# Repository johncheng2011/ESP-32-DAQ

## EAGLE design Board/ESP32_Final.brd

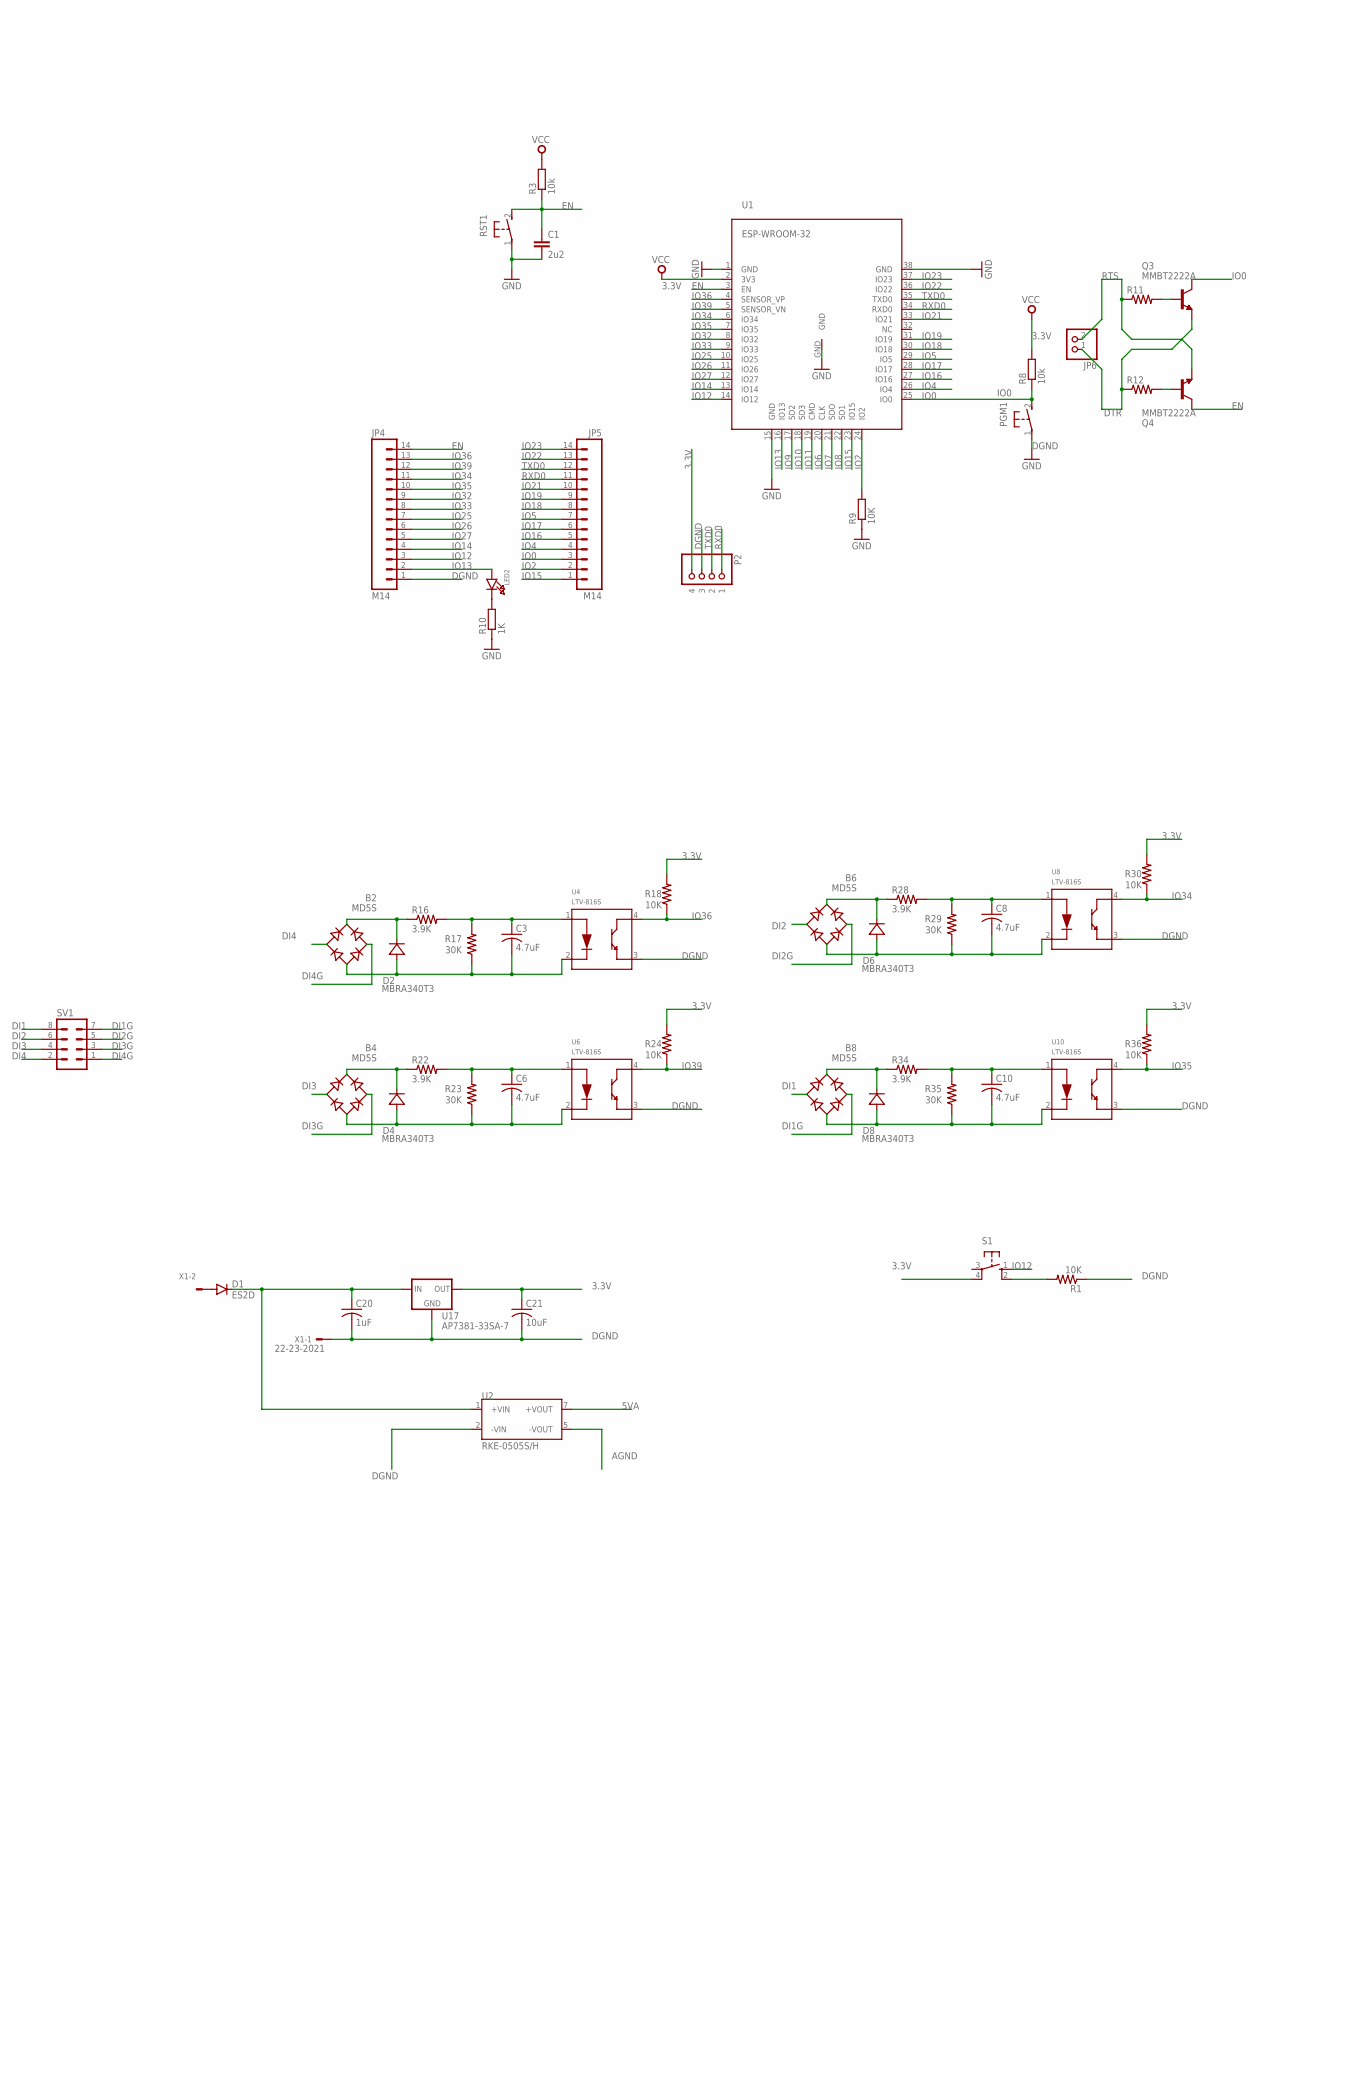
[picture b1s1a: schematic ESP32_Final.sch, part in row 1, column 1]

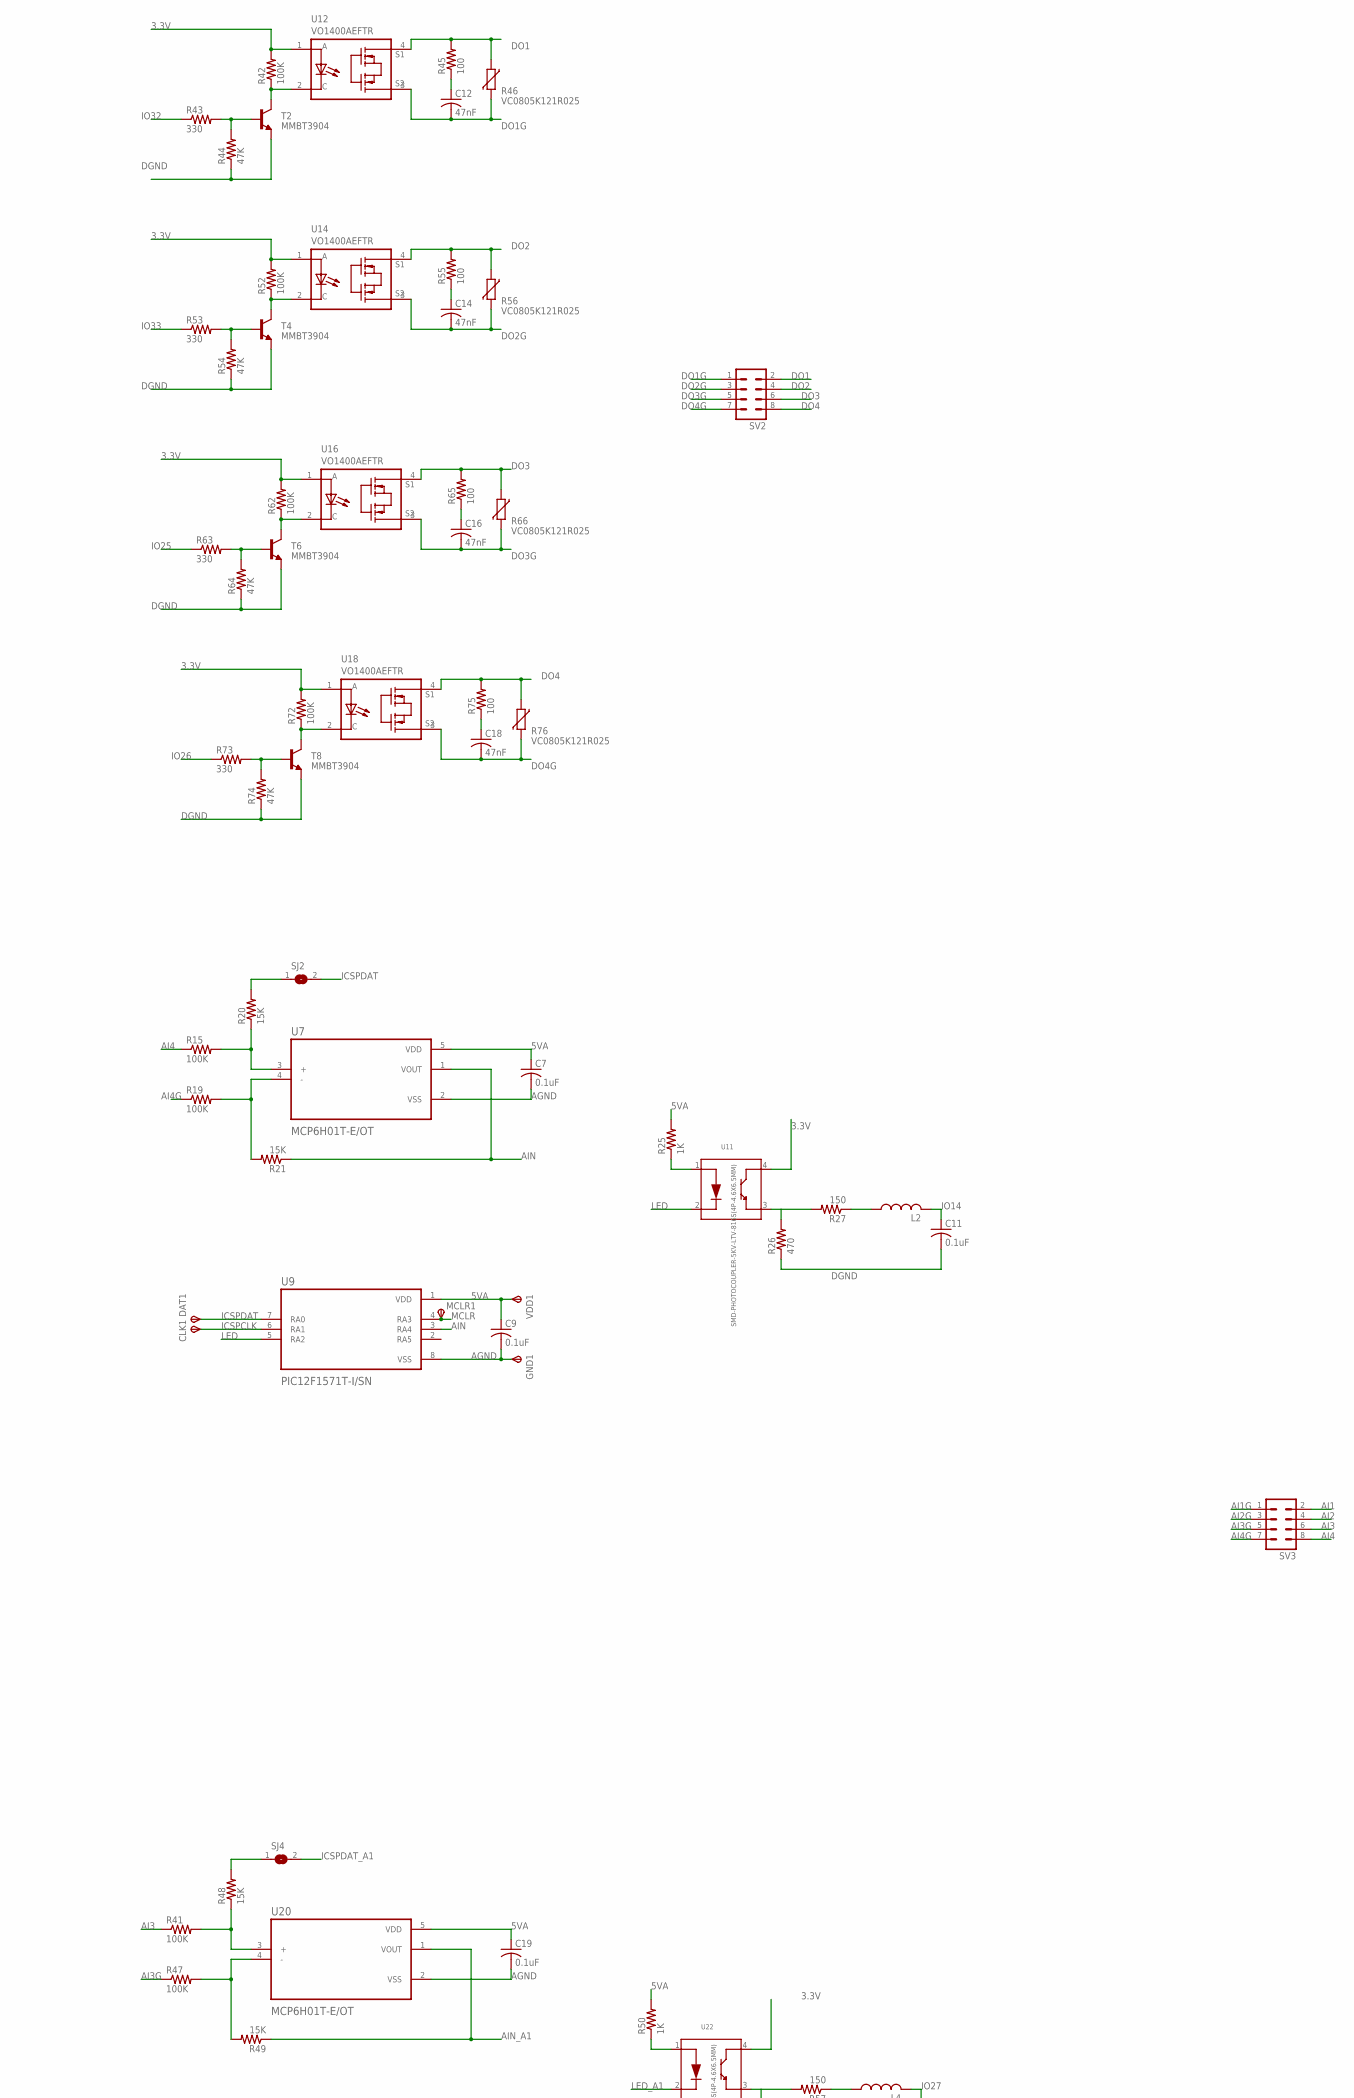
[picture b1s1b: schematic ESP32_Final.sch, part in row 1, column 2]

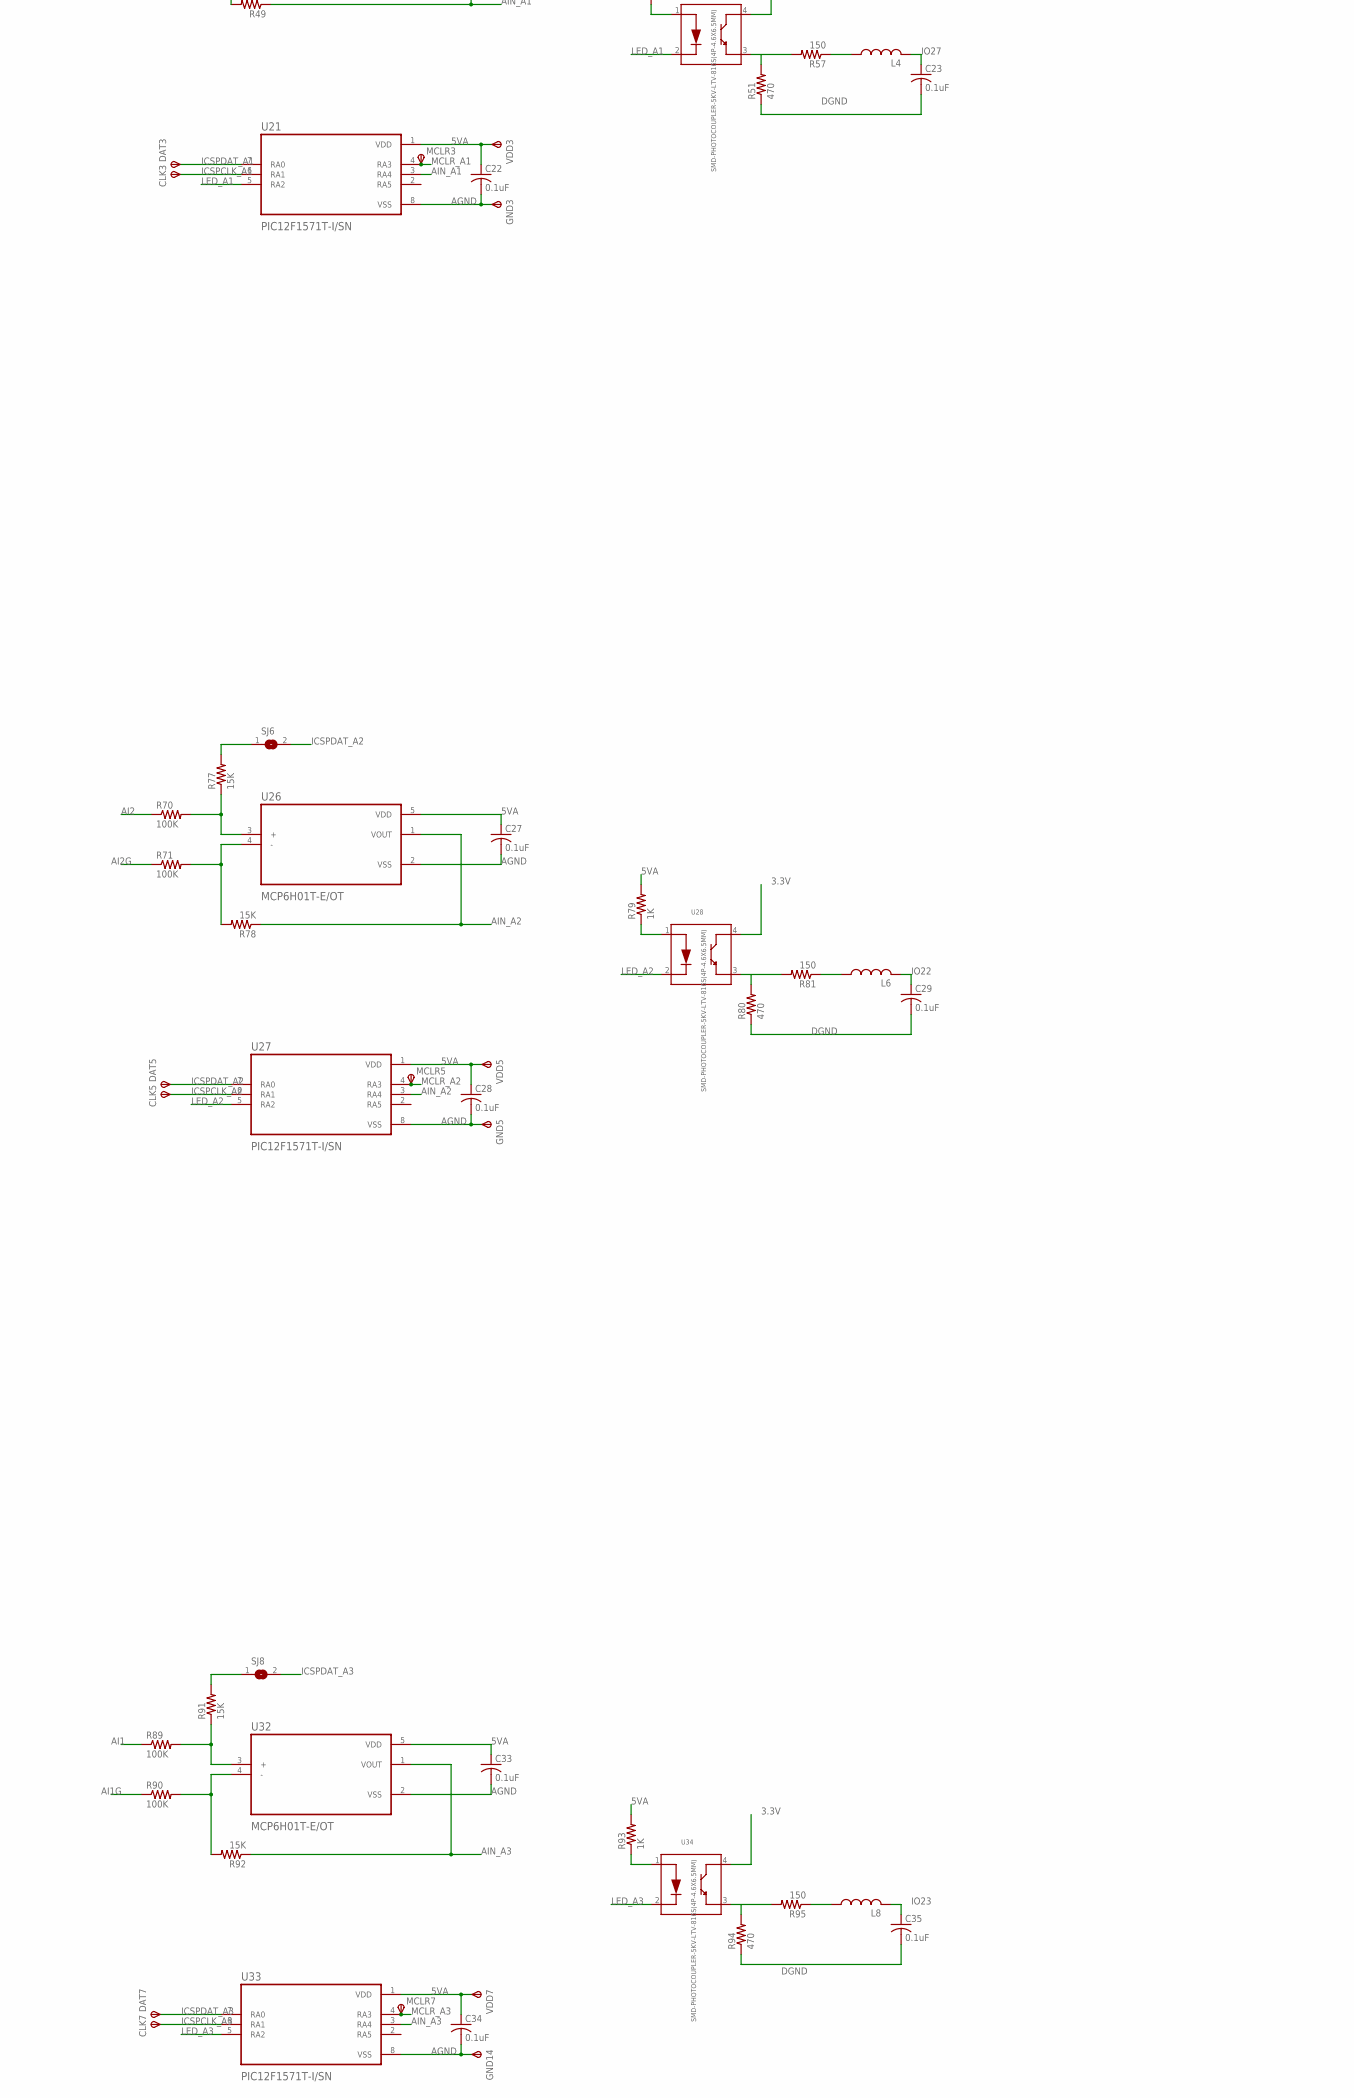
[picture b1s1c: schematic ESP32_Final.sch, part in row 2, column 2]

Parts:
B2, B4, B6, B8: MD5S; TO-269AA
C1: 2u2; C0603
C3, C6, C8, C10: 4.7uF; C0805
C7, C9, C11, C19, C22, C23, C27, C28, C29, C33, C34, C35: 0.1uF; C0603
C12, C14, C16, C18: 47nF; C0805
C20: 1uF; C0603
C21: 10uF; C0603
CLK1, CLK3, CLK5, CLK7: TPSTP14R; TP14R
D1: ES2D; SMB
D2, D4, D6, D8: MBRA340T3; SMA
DAT1, DAT3, DAT5, DAT7: TPSTP14R; TP14R
GND1, GND3, GND5, GND14: TPSTP14R; TP14R
JP4, JP5: M14; 1X14
JP6: HEADER-1X2ROUND; 1X02_ROUND
L2, L4, L6, L8: L-USL2012C; L2012C
LED2: LED0603; CHIPLED_0603
MCLR1, MCLR3, MCLR5, MCLR7: TPSTP14R; TP14R
P2: HEADER-1X4ROUND; 1X04_ROUND
PGM1: DTSM-3
Q3, Q4: MMBT2222A; SOT23
R1: 10K; R0805
R3, R8: 10k; R0603@1
R9: 10K; R0603@1
R10: 1K; R0603@1
R11, R12: R-US_R0603; R0603
R15, R19, R41, R47, R70, R71, R89, R90: 100K; R0805
R16, R22, R28, R34: 3.9K; R0805
R17, R23, R29, R35: 30K; R0805
R18, R24, R30, R36: 10K; R0603
R20, R21, R48, R49, R77, R78, R91, R92: 15K; R0603
R25, R50, R79, R93: 1K; R0805
R26, R51, R80, R94: 470; R0805
R27, R57, R81, R95: 150; R0805
R42, R52, R62, R72: 100K; R0603
R43, R53, R63, R73: 330; R0603
R44, R54, R64, R74: 47K; R0603
R45, R55, R65, R75: 100; R1210
R46, R56, R66, R76: VC0805K121R025; CT/CN0805
RST1: DTSM-3
S1: 10-XX; B3F-10XX
SJ2, SJ4, SJ6, SJ8: SJ
SV1, SV2, SV3: MA04-2
T2, T4, T6, T8: MMBT3904; SOT23-BEC
U1: ESP-WROOM-32
U2: RKE-0505S/H; CONV_RKE-0505S/H
U4, U6, U8, U10: LTV-816S; SMD4-2.54-4.6X6.5MM
U7, U20, U26, U32: MCP6H01T-E/OT; SOT95P280X145-5N
U9, U21, U27, U33: PIC12F1571T-I/SN; SOIC127P600X175-8N
U11, U22, U28, U34: SMD-PHOTOCOUPLER-5KV-LTV-816S(4P-4.6X6.5MM); SMD4-2.54-4.6X6.5MM
U12, U14, U16, U18: VO1400AEFTR; SOIC254P695X242-4N
U17: AP7381-33SA-7; SOT23
VDD1, VDD3, VDD5, VDD7: TPSTP14R; TP14R
X1: 22-23-2021

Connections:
3.3V: C21.1, P2.4, R3.2, R8.2, R18.2, R24.2, R30.2, R36.2, R42.2, R52.2, R62.2, R72.2, S1.4 (P1), U1.2 (3V3), U11.4 (COLLECTOR), U12.1 (A), U14.1 (A), U16.1 (A), U17.2 (OUT), U18.1 (A), U22.4 (COLLECTOR), U28.4 (COLLECTOR), U34.4 (COLLECTOR)
5VA: C7.1, C9.1, C19.1, C22.1, C27.1, C28.1, C33.1, C34.1, R25.2, R50.2, R79.2, R93.2, U2.7 (+VOUT), U7.5 (VDD), U9.1 (VDD), U20.5 (VDD), U21.1 (VDD), U26.5 (VDD), U27.1 (VDD), U32.5 (VDD), U33.1 (VDD), VDD1.TP, VDD3.TP, VDD5.TP, VDD7.TP
AGND: C7.2, C9.2, C19.2, C22.2, C27.2, C28.2, C33.2, C34.2, GND1.TP, GND3.TP, GND5.TP, GND14.TP, U2.5 (-VOUT), U7.2 (VSS), U9.8 (VSS), U20.2 (VSS), U21.8 (VSS), U26.2 (VSS), U27.8 (VSS), U32.2 (VSS), U33.8 (VSS)
AI1: R89.1, SV3.2
AI1G: R90.1, SV3.1
AI2: R70.1, SV3.4
AI2G: R71.1, SV3.3
AI3: R41.1, SV3.6
AI3G: R47.1, SV3.5
AI4: R15.1, SV3.8
AI4G: R19.1, SV3.7
AIN: R21.1, U7.1 (VOUT), U9.3 (RA4)
AIN_A1: R49.1, U20.1 (VOUT), U21.3 (RA4)
AIN_A2: R78.1, U26.1 (VOUT), U27.3 (RA4)
AIN_A3: R92.1, U32.1 (VOUT), U33.3 (RA4)
DGND: C1.2, C11.2, C20.2, C21.2, C23.2, C29.2, C35.2, JP4.1, P2.3, PGM1.1, R1.1, R9.1, R10.1, R26.1, R44.1, R51.1, R54.1, R64.1, R74.1, R80.1, R94.1, RST1.1, T2.E, T4.E, T6.E, T8.E, U1.1 (GND), U1.15 (GND), U1.38 (GND), U1.GND, U2.2 (-VIN), U4.3 (EMITER), U6.3 (EMITER), U8.3 (EMITER), U10.3 (EMITER), U17.3 (GND), X1.1
DI1: B8.AC1, SV1.8
DI1G: B8.AC2, SV1.7
DI2: B6.AC1, SV1.6
DI2G: B6.AC2, SV1.5
DI3: B4.AC1, SV1.4
DI3G: B4.AC2, SV1.3
DI4: B2.AC1, SV1.2
DI4G: B2.AC2, SV1.1
DO1: R45.2, R46.1, SV2.2, U12.4 (S1)
DO1G: C12.2, R46.2, SV2.1, U12.3 (S2)
DO2: R55.2, R56.1, SV2.4, U14.4 (S1)
DO2G: C14.2, R56.2, SV2.3, U14.3 (S2)
DO3: R65.2, R66.1, SV2.6, U16.4 (S1)
DO3G: C16.2, R66.2, SV2.5, U16.3 (S2)
DO4: R75.2, R76.1, SV2.8, U18.4 (S1)
DO4G: C18.2, R76.2, SV2.7, U18.3 (S2)
DTR: JP6.1, Q3.2 (E), R12.1
EN: C1.1, JP4.14, Q4.3 (C), R3.1, RST1.2, U1.3 (EN)
ICSPCLK: CLK1.TP, U9.6 (RA1)
ICSPCLK_A1: CLK3.TP, U21.6 (RA1)
ICSPCLK_A2: CLK5.TP, U27.6 (RA1)
ICSPCLK_A3: CLK7.TP, U33.6 (RA1)
ICSPDAT: DAT1.TP, SJ2.2, U9.7 (RA0)
ICSPDAT_A1: DAT3.TP, SJ4.2, U21.7 (RA0)
ICSPDAT_A2: DAT5.TP, SJ6.2, U27.7 (RA0)
ICSPDAT_A3: DAT7.TP, SJ8.2, U33.7 (RA0)
IO0: JP5.3, PGM1.2, Q3.3 (C), R8.1, U1.25 (IO0)
IO2: JP5.2, R9.2, U1.24 (IO2)
IO4: JP5.4, U1.26 (IO4)
IO5: JP5.7, U1.29 (IO5)
IO6: U1.20 (CLK)
IO7: U1.21 (SDO)
IO8: U1.22 (SD1)
IO9: U1.17 (SD2)
IO10: U1.18 (SD3)
IO11: U1.19 (CMD)
IO12: JP4.3, S1.1 (S), U1.14 (IO12)
IO13: JP4.2, LED2.A, U1.16 (IO13)
IO14: C11.1, JP4.4, L2.2, U1.13 (IO14)
IO15: JP5.1, U1.23 (IO15)
IO16: JP5.5, U1.27 (IO16)
IO17: JP5.6, U1.28 (IO17)
IO18: JP5.8, U1.30 (IO18)
IO19: JP5.9, U1.31 (IO19)
IO21: JP5.10, U1.33 (IO21)
IO22: C29.1, JP5.13, L6.2, U1.36 (IO22)
IO23: C35.1, JP5.14, L8.2, U1.37 (IO23)
IO25: JP4.7, R63.1, U1.10 (IO25)
IO26: JP4.6, R73.1, U1.11 (IO26)
IO27: C23.1, JP4.5, L4.2, U1.12 (IO27)
IO32: JP4.9, R43.1, U1.8 (IO32)
IO33: JP4.8, R53.1, U1.9 (IO33)
IO34: JP4.11, R30.1, U1.6 (IO34), U8.4 (COLLECTOR)
IO35: JP4.10, R36.1, U1.7 (IO35), U10.4 (COLLECTOR)
IO36: JP4.13, R18.1, U1.4 (SENSOR_VP), U4.4 (COLLECTOR)
IO39: JP4.12, R24.1, U1.5 (SENSOR_VN), U6.4 (COLLECTOR)
LED: U9.5 (RA2), U11.2 (CATHODE)
LED_A1: U21.5 (RA2), U22.2 (CATHODE)
LED_A2: U27.5 (RA2), U28.2 (CATHODE)
LED_A3: U33.5 (RA2), U34.2 (CATHODE)
MCLR: MCLR1.TP, U9.4 (RA3)
MCLR_A1: MCLR3.TP, U21.4 (RA3)
MCLR_A2: MCLR5.TP, U27.4 (RA3)
MCLR_A3: MCLR7.TP, U33.4 (RA3)
unnamed: LED2.C, R10.2
unnamed: D1.A, X1.2
unnamed: Q3.1 (B), R11.2
unnamed: Q4.1 (B), R12.2
unnamed: R1.2, S1.2 (S1)
unnamed: R15.2, R20.1, U7.3 (+)
unnamed: C3.1, R16.2, R17.2, U4.1 (ANODE)
unnamed: B2.-, C3.2, D2.A, R17.1, U4.2 (CATHODE)
unnamed: B2.+, D2.C, R16.1
unnamed: R19.2, R21.2, U7.4 (-)
unnamed: R20.2, SJ2.1
unnamed: R25.1, U11.1 (ANODE)
unnamed: R26.2, R27.2, U11.3 (EMITER)
unnamed: L2.1, R27.1
unnamed: C6.1, R22.2, R23.2, U6.1 (ANODE)
unnamed: B4.-, C6.2, D4.A, R23.1, U6.2 (CATHODE)
unnamed: B4.+, D4.C, R22.1
unnamed: R41.2, R48.1, U20.3 (+)
unnamed: R47.2, R49.2, U20.4 (-)
unnamed: R48.2, SJ4.1
unnamed: R50.1, U22.1 (ANODE)
unnamed: R51.2, R57.2, U22.3 (EMITER)
unnamed: C20.1, D1.C, U2.1 (+VIN), U17.1 (IN)
unnamed: C8.1, R28.2, R29.2, U8.1 (ANODE)
unnamed: B6.-, C8.2, D6.A, R29.1, U8.2 (CATHODE)
unnamed: B6.+, D6.C, R28.1
unnamed: L4.1, R57.1
unnamed: C10.1, R34.2, R35.2, U10.1 (ANODE)
unnamed: B8.-, C10.2, D8.A, R35.1, U10.2 (CATHODE)
unnamed: B8.+, D8.C, R34.1
unnamed: R70.2, R77.1, U26.3 (+)
unnamed: R71.2, R78.2, U26.4 (-)
unnamed: R77.2, SJ6.1
unnamed: R79.1, U28.1 (ANODE)
unnamed: R80.2, R81.2, U28.3 (EMITER)
unnamed: L6.1, R81.1
unnamed: R42.1, T2.C, U12.2 (C)
unnamed: R43.2, R44.2, T2.B
unnamed: C12.1, R45.1
unnamed: R89.2, R91.1, U32.3 (+)
unnamed: R90.2, R92.2, U32.4 (-)
unnamed: R91.2, SJ8.1
unnamed: R93.1, U34.1 (ANODE)
unnamed: R52.1, T4.C, U14.2 (C)
unnamed: R53.2, R54.2, T4.B
unnamed: R94.2, R95.2, U34.3 (EMITER)
unnamed: C14.1, R55.1
unnamed: L8.1, R95.1
unnamed: R62.1, T6.C, U16.2 (C)
unnamed: R63.2, R64.2, T6.B
unnamed: C16.1, R65.1
unnamed: R72.1, T8.C, U18.2 (C)
unnamed: R73.2, R74.2, T8.B
unnamed: C18.1, R75.1
RTS: JP6.2, Q4.2 (E), R11.1
RXD0: JP5.11, P2.1, U1.34 (RXD0)
TXD0: JP5.12, P2.2, U1.35 (TXD0)

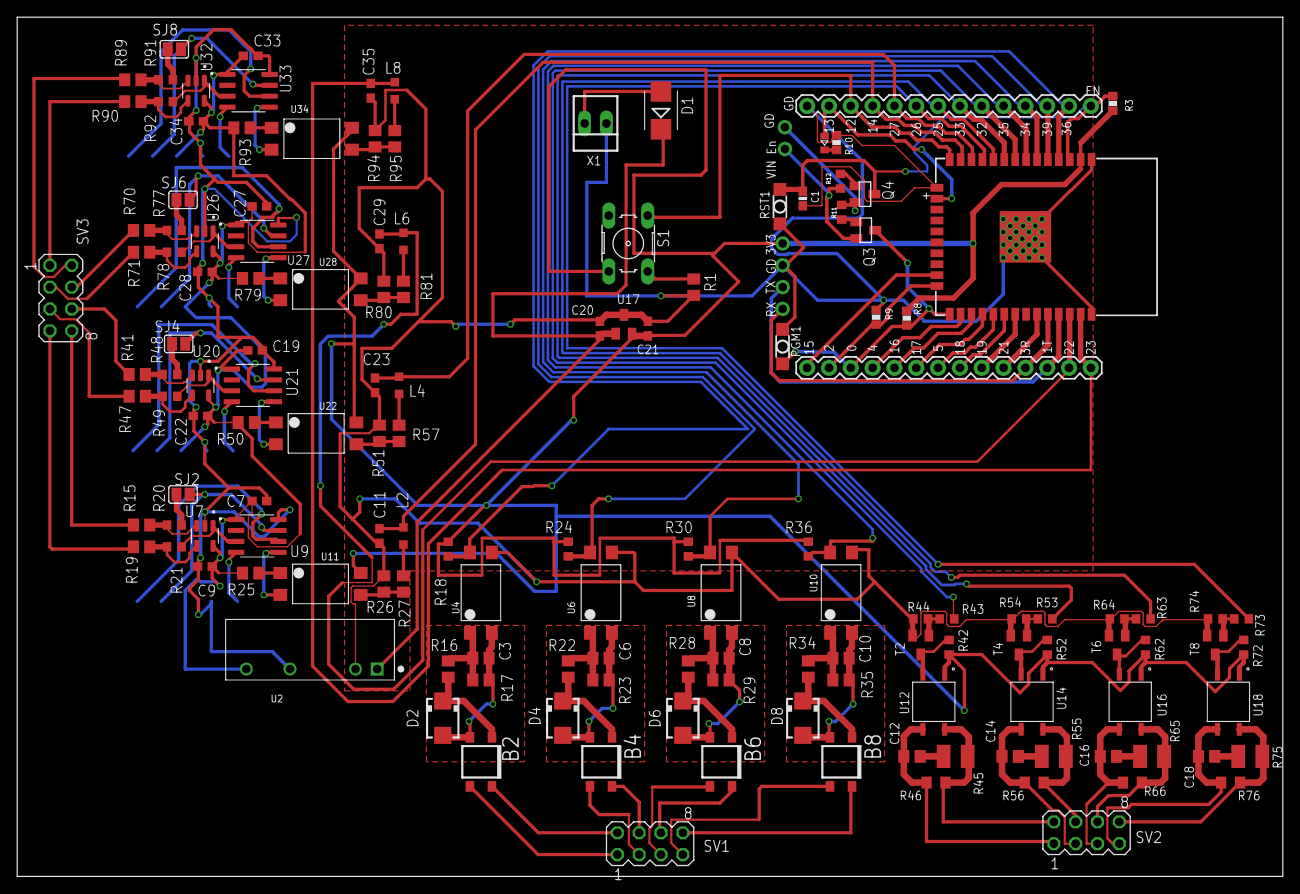
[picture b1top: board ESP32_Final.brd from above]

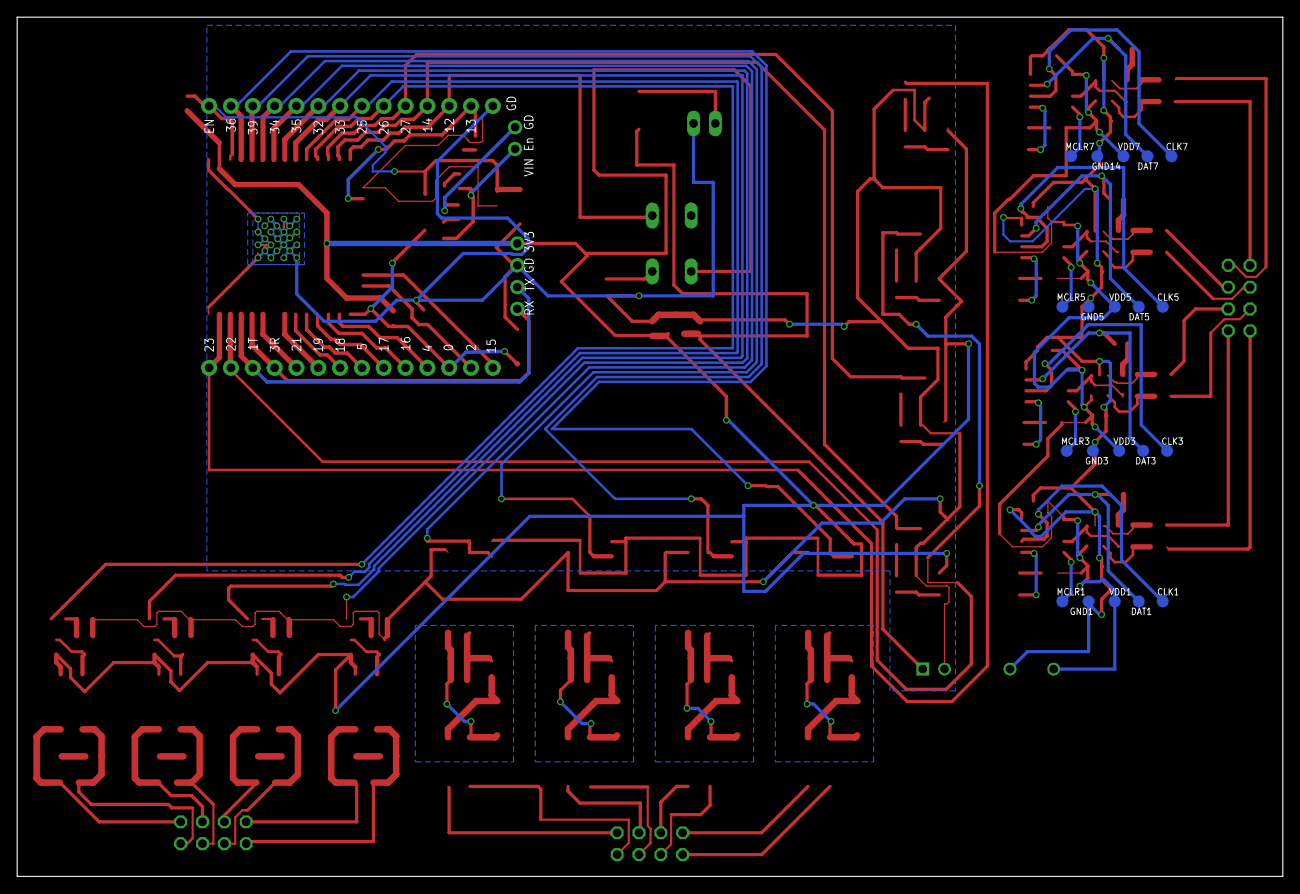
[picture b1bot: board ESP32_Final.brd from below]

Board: 2 copper layers, 147.3 x 100.0 mm, 168 parts (20 on the bottom side), 131 nets.

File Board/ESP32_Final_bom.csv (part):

"Part","Value","Device","Package","Description","AVAILABILITY","DESCRIPTION","MF","MP","MPN","OC_FARNELL","OC_NEWARK","PACKAGE","PRICE","SPICEPREFIX","TP_SIGNAL_NAME",
"B2","MD5S","RECTIFIER-S80","TO-269AA","Rectifier","","","","","","","","","","","",
"B4","MD5S","RECTIFIER-S80","TO-269AA","Rectifier","","","","","","","","","","","",
"B6","MD5S","RECTIFIER-S80","TO-269AA","Rectifier","","","","","","","","","","","",
"B8","MD5S","RECTIFIER-S80","TO-269AA","Rectifier","","","","","","","","","","","",
"C1","2u2","C-EUC0603","C0603","CAPACITOR, European symbol","","","","","","","","","","","",
"C3","4.7uF","C-USC0805","C0805","CAPACITOR, American symbol","","","","","","","","","","C","",
"C6","4.7uF","C-USC0805","C0805","CAPACITOR, American symbol","","","","","","","","","","C","",
"C7","0.1uF","C-USC0603","C0603","CAPACITOR, American symbol","","","","","","","","","","C","",
"C8","4.7uF","C-USC0805","C0805","CAPACITOR, American symbol","","","","","","","","","","C","",
"C9","0.1uF","C-USC0603","C0603","CAPACITOR, American symbol","","","","","","","","","","C","",
"C10","4.7uF","C-USC0805","C0805","CAPACITOR, American symbol","","","","","","","","","","C","",
"C11","0.1uF","C-USC0603","C0603","CAPACITOR, American symbol","","","","","","","","","","C","",
"C12","47nF","C-USC0805","C0805","CAPACITOR, American symbol","","","","","","","","","","C","",
"C14","47nF","C-USC0805","C0805","CAPACITOR, American symbol","","","","","","","","","","C","",
"C16","47nF","C-USC0805","C0805","CAPACITOR, American symbol","","","","","","","","","","C","",
"C18","47nF","C-USC0805","C0805","CAPACITOR, American symbol","","","","","","","","","","C","",
"C19","0.1uF","C-USC0603","C0603","CAPACITOR, American symbol","","","","","","","","","","C","",
"C20","1uF","C-USC0603","C0603","CAPACITOR, American symbol","","","","","","","","","","C","",
"C21","10uF","C-USC0603","C0603","CAPACITOR, American symbol","","","","","","","","","","C","",
"C22","0.1uF","C-USC0603","C0603","CAPACITOR, American symbol","","","","","","","","","","C","",
"C23","0.1uF","C-USC0603","C0603","CAPACITOR, American symbol","","","","","","","","","","C","",
"C27","0.1uF","C-USC0603","C0603","CAPACITOR, American symbol","","","","","","","","","","C","",
"C28","0.1uF","C-USC0603","C0603","CAPACITOR, American symbol","","","","","","","","","","C","",
"C29","0.1uF","C-USC0603","C0603","CAPACITOR, American symbol","","","","","","","","","","C","",
"C33","0.1uF","C-USC0603","C0603","CAPACITOR, American symbol","","","","","","","","","","C","",
"C34","0.1uF","C-USC0603","C0603","CAPACITOR, American symbol","","","","","","","","","","C","",
"C35","0.1uF","C-USC0603","C0603","CAPACITOR, American symbol","","","","","","","","","","C","",
"CLK1","TPSTP14R","TPSTP14R","TP14R","TEST PIN","","","","","","","","","","","",
"CLK3","TPSTP14R","TPSTP14R","TP14R","TEST PIN","","","","","","","","","","","",
"CLK5","TPSTP14R","TPSTP14R","TP14R","TEST PIN","","","","","","","","","","","",
"CLK7","TPSTP14R","TPSTP14R","TP14R","TEST PIN","","","","","","","","","","","",
"D1","ES2D","ES2D","SMB","DIODE","","","","","","","","","","","",
"D2","MBRA340T3","MBRA340T3","SMA","Surface Mount Schottky Power Rectifier","","","","","","","","","","","",
"D4","MBRA340T3","MBRA340T3","SMA","Surface Mount Schottky Power Rectifier","","","","","","","","","","","",
"D6","MBRA340T3","MBRA340T3","SMA","Surface Mount Schottky Power Rectifier","","","","","","","","","","","",
"D8","MBRA340T3","MBRA340T3","SMA","Surface Mount Schottky Power Rectifier","","","","","","","","","","","",
"DAT1","TPSTP14R","TPSTP14R","TP14R","TEST PIN","","","","","","","","","","","",
"DAT3","TPSTP14R","TPSTP14R","TP14R","TEST PIN","","","","","","","","","","","",
"DAT5","TPSTP14R","TPSTP14R","TP14R","TEST PIN","","","","","","","","","","","",
"DAT7","TPSTP14R","TPSTP14R","TP14R","TEST PIN","","","","","","","","","","","",
"GND1","TPSTP14R","TPSTP14R","TP14R","TEST PIN","","","","","","","","","","","",
"GND3","TPSTP14R","TPSTP14R","TP14R","TEST PIN","","","","","","","","","","","",
"GND5","TPSTP14R","TPSTP14R","TP14R","TEST PIN","","","","","","","","","","","",
"GND14","TPSTP14R","TPSTP14R","TP14R","TEST PIN","","","","","","","","","","","",
"JP4","M14","M14","1X14","Header 14","","","","","","","","","","","",
"JP5","M14","M14","1X14","Header 14","","","","","","","","","","","",
"JP6","","HEADER-1X2ROUND","1X02_ROUND","PIN HEADER","","","","","","","","","","","",
"L2","","L-USL2012C","L2012C","INDUCTOR, American symbol","","","","","","","","","","L","",
"L4","","L-USL2012C","L2012C","INDUCTOR, American symbol","","","","","","","","","","L","",
"L6","","L-USL2012C","L2012C","INDUCTOR, American symbol","","","","","","","","","","L","",
"L8","","L-USL2012C","L2012C","INDUCTOR, American symbol","","","","","","","","","","L","",
"LED2","","LED0603","CHIPLED_0603","LED","","","","","","","","","","","",
"MCLR1","TPSTP14R","TPSTP14R","TP14R","TEST PIN","","","","","","","","","","","",
"MCLR3","TPSTP14R","TPSTP14R","TP14R","TEST PIN","","","","","","","","","","","",
"MCLR5","TPSTP14R","TPSTP14R","TP14R","TEST PIN","","","","","","","","","","","",
"MCLR7","TPSTP14R","TPSTP14R","TP14R","TEST PIN","","","","","","","","","","","",
"P2","","HEADER-1X4ROUND","1X04_ROUND","PIN HEADER","","","","","","","","","","","",
"PGM1","DTSM-3","DTSM-3","DTSM-3","","","","","","","","","","","","",
"Q3","MMBT2222A","MMBT2222A","SOT23","2N2222 General Purpose NPN Transistor","Unavailable"," ","STMicroelectronics","MMBT2222A","","","","TO-236-3 Taitron","None","","",
"Q4","MMBT2222A","MMBT2222A","SOT23","2N2222 General Purpose NPN Transistor","Unavailable"," ","STMicroelectronics","MMBT2222A","","","","TO-236-3 Taitron","None","","",
"R1","10K","R-US_R0805","R0805","RESISTOR, American symbol","","","","","","","","","","R","",
"R3","10k","R-EU_R0603","R0603@1","RESISTOR, European symbol","","","","","","","","","","","",
"R8","10k","R-EU_R0603","R0603@1","RESISTOR, European symbol","","","","","","","","","","","",
"R9","10K","R-EU_R0603","R0603@1","RESISTOR, European symbol","","","","","","","","","","","",
"R10","1K","R-EU_R0603","R0603@1","RESISTOR, European symbol","","","","","","","","","","","",
"R11","","R-US_R0603","R0603","RESISTOR, American symbol","","","","","","","","","","R","",
"R12","","R-US_R0603","R0603","RESISTOR, American symbol","","","","","","","","","","R","",
"R15","100K","R-US_R0805","R0805","RESISTOR, American symbol","","","","","","","","","","R","",
"R16","3.9K","R-US_R0805","R0805","RESISTOR, American symbol","","","","","","","","","","R","",
"R17","30K","R-US_R0805","R0805","RESISTOR, American symbol","","","","","","","","","","R","",
"R18","10K","R-US_R0603","R0603","RESISTOR, American symbol","","","","","","","","","","","",
"R19","100K","R-US_R0805","R0805","RESISTOR, American symbol","","","","","","","","","","R","",
"R20","15K","R-US_R0603","R0603","RESISTOR, American symbol","","","","","","","","","","R","",
"R21","15K","R-US_R0603","R0603","RESISTOR, American symbol","","","","","","","","","","R","",
"R22","3.9K","R-US_R0805","R0805","RESISTOR, American symbol","","","","","","","","","","R","",
"R23","30K","R-US_R0805","R0805","RESISTOR, American symbol","","","","","","","","","","R","",
"R24","10K","R-US_R0603","R0603","RESISTOR, American symbol","","","","","","","","","","","",
"R25","1K","R-US_R0805","R0805","RESISTOR, American symbol","","","","","","","","","","R","",
"R26","470","R-US_R0805","R0805","RESISTOR, American symbol","","","","","","","","","","R","",
"R27","150","R-US_R0805","R0805","RESISTOR, American symbol","","","","","","","","","","R","",
"R28","3.9K","R-US_R0805","R0805","RESISTOR, American symbol","","","","","","","","","","R","",
"R29","30K","R-US_R0805","R0805","RESISTOR, American symbol","","","","","","","","","","R","",
"R30","10K","R-US_R0603","R0603","RESISTOR, American symbol","","","","","","","","","","","",
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
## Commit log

2019-06-06 Initial

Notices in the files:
parts and their libraries:
SparkFun-Connectors: Licensing: Creative Commons ShareAlike 4.0 International - https://creativecommons.org/licenses/by-sa/4.0
